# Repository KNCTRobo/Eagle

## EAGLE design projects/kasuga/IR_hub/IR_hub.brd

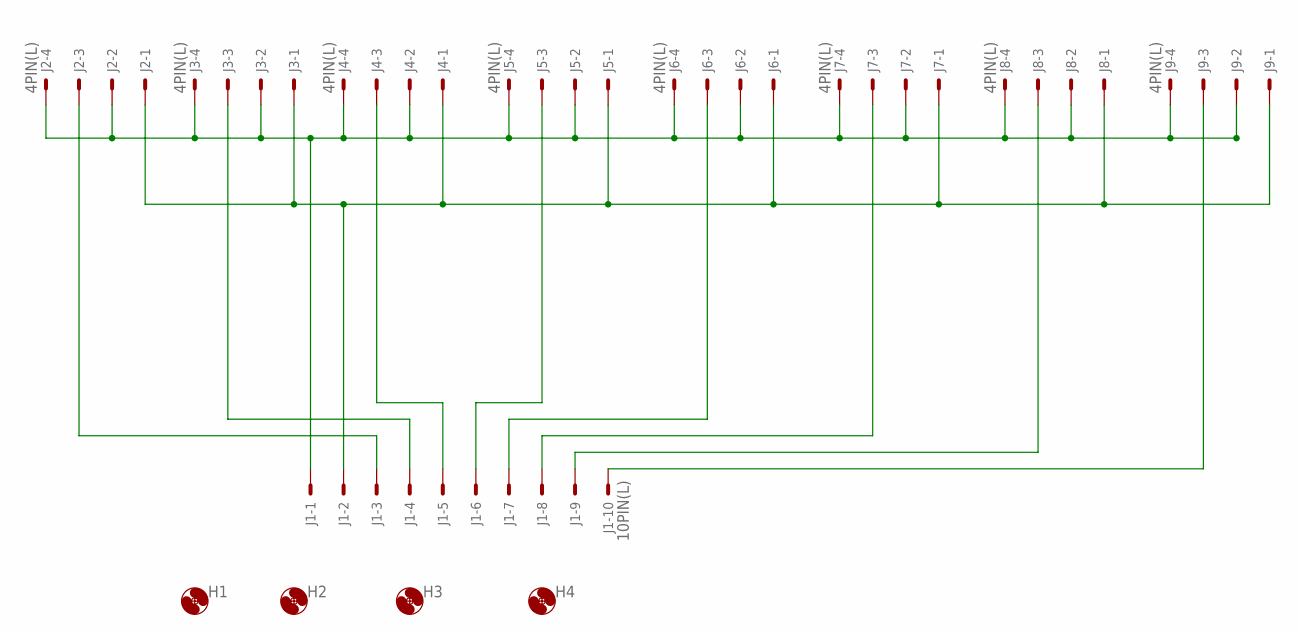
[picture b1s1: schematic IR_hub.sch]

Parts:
H1, H2, H3, H4: HOLE3.3M3BOLT; HOLE3.3
J1: 10PIN(L); 10PL
J2, J3, J4, J5, J6, J7, J8, J9: 4PIN(L); 4PL

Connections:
unnamed: J1.10, J9.3
unnamed: J1.9, J8.3
unnamed: J1.8, J7.3
unnamed: J1.7, J6.3
unnamed: J1.6, J5.3
unnamed: J1.5, J4.3
unnamed: J1.4, J3.3
unnamed: J1.3, J2.3
unnamed: J1.1, J2.2, J2.4, J3.2, J3.4, J4.2, J4.4, J5.2, J5.4, J6.2, J6.4, J7.2, J7.4, J8.2, J8.4, J9.2, J9.4
unnamed: J1.2, J2.1, J3.1, J4.1, J5.1, J6.1, J7.1, J8.1, J9.1

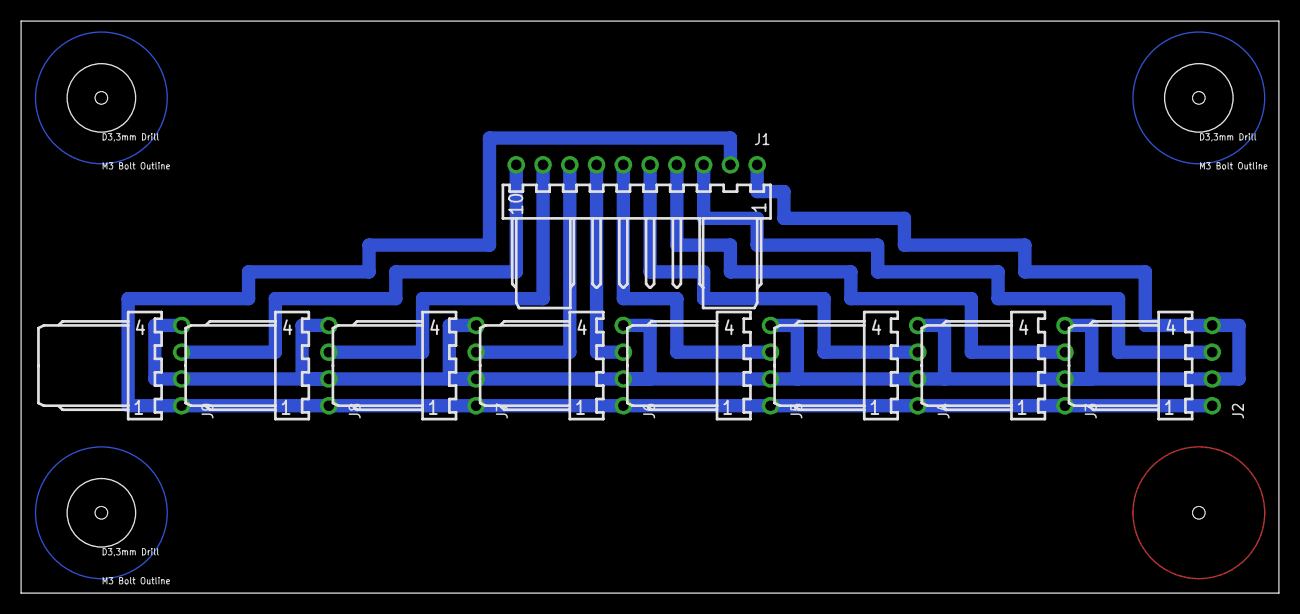
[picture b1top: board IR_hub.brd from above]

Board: 2 copper layers, 119.4 x 54.3 mm, 13 parts (1 on the bottom side), 10 nets.

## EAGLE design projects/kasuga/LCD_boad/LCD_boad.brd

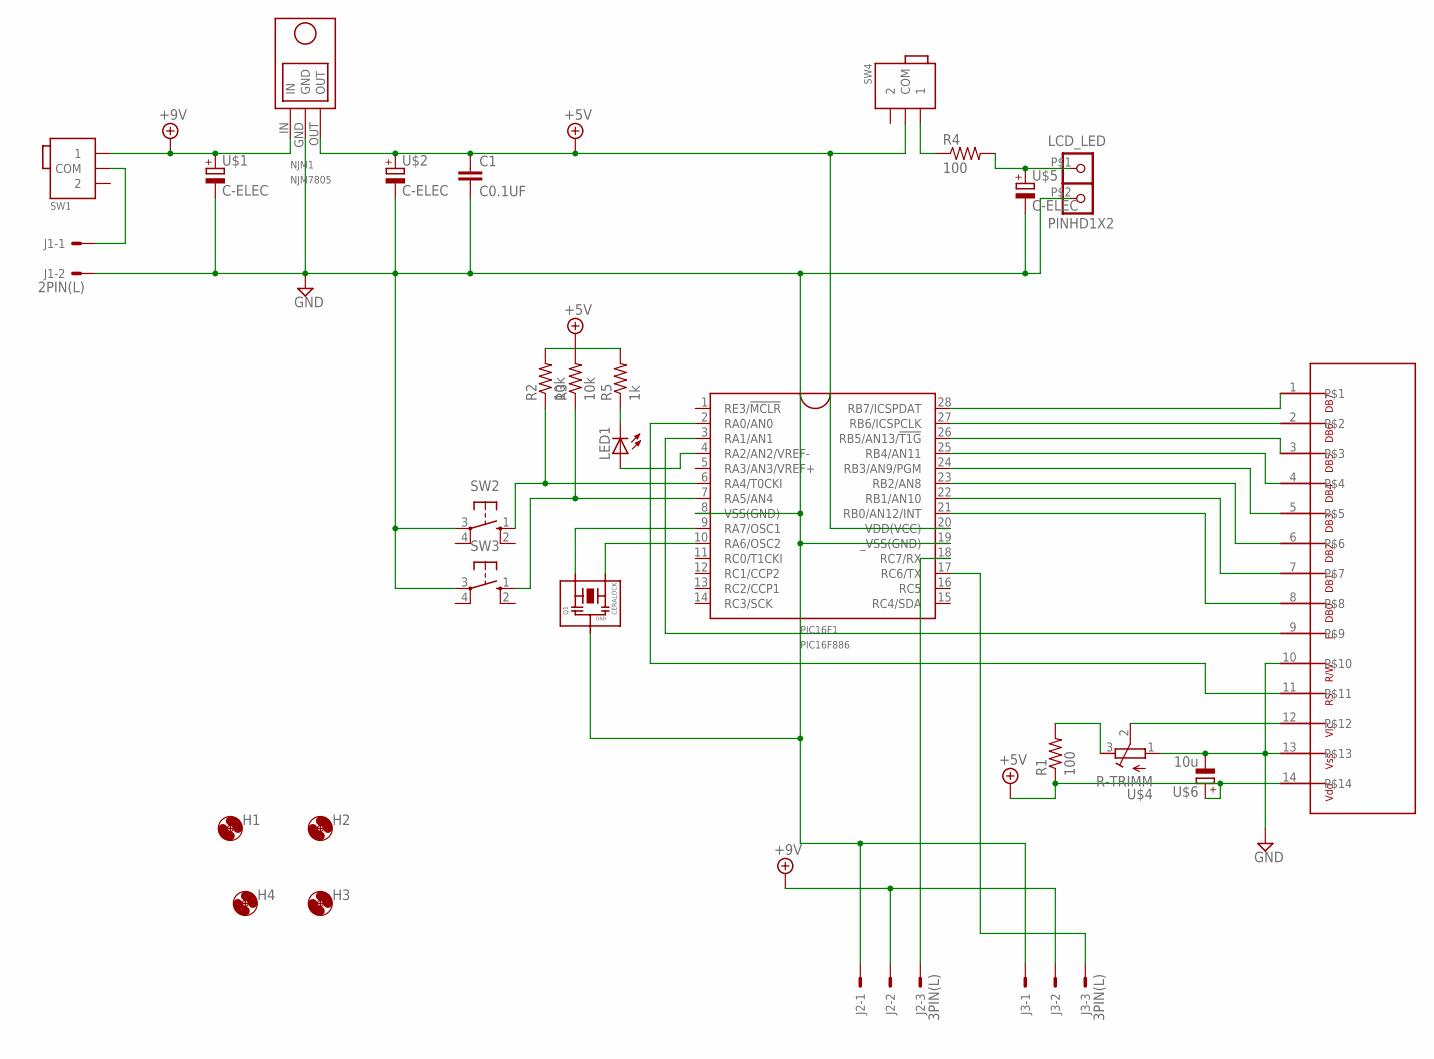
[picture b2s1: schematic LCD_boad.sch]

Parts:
C1: C0.1UF
H1, H2, H3, H4: HOLE3.3M3BOLT; HOLE3.3
J1: 2PIN(L); 2PL
J2, J3: 3PIN(L); 3PL
LCD_LED: PINHD1X2
LED1: LED; LED5MM
NJM1: NJM7805
PIC16F1: PIC16F886; DIL28-3
Q1: CERALOCK
R1, R4: 100; 0207/10
R2, R3: 10k; 0207/10
R5: 1k; 0207/10
SW1, SW4: SWITCH_MININORMAL; SWITCH_MINI
SW2, SW3: TACTSW; TACT
U$1, U$2, U$5: C-ELEC; C-6MM
U$3: L1672D1JOOO; Ｌ１６７２Ｄ１Ｊ０００
U$4: R-TRIMM
U$6: 10u; C-6MM

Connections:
+5V: C1.1, NJM1.OUT, PIC16F1.20 (VDD(VCC)), R1.1, R2.2, R3.2, R5.2, SW4.COM, U$2.+, U$3.14, U$6.+
+9V: J2.2, J3.2, NJM1.IN, SW1.1, U$1.+
GND: C1.2, J1.2, J2.1, J3.1, LCD_LED.P$2 (3), NJM1.GND, PIC16F1.8 (VSS(GND)), PIC16F1.19 (_VSS(GND)), Q1.P$2, SW2.3, SW3.3, U$1.-, U$2.-, U$3.10, U$3.13, U$4.1, U$5.-, U$6.-
unnamed: J1.1, SW1.COM
unnamed: J2.3, PIC16F1.18 (RC7/RX)
unnamed: R1.2, U$4.3
unnamed: J3.3, PIC16F1.17 (RC6/TX)
unnamed: PIC16F1.28 (RB7/ICSPDAT), U$3.1
unnamed: PIC16F1.27 (RB6/ICSPCLK), U$3.2
unnamed: PIC16F1.26 (RB5/AN13/!T1G), U$3.3
unnamed: PIC16F1.25 (RB4/AN11), U$3.4
unnamed: PIC16F1.24 (RB3/AN9/PGM), U$3.5
unnamed: PIC16F1.23 (RB2/AN8), U$3.6
unnamed: PIC16F1.22 (RB1/AN10), U$3.7
unnamed: PIC16F1.21 (RB0/AN12/INT), U$3.8
unnamed: PIC16F1.3 (RA1/AN1), U$3.9
unnamed: PIC16F1.2 (RA0/AN0), U$3.11
unnamed: U$3.12, U$4.2
unnamed: PIC16F1.6 (RA4/T0CKI), R2.1, SW2.1 (S)
unnamed: PIC16F1.7 (RA5/AN4), R3.1, SW3.1 (S)
unnamed: LCD_LED.P$1 (4), R4.2, U$5.+
unnamed: R4.1, SW4.1
unnamed: LED1.A, PIC16F1.4 (RA2/AN2/VREF-)
unnamed: LED1.K (C), R5.1
unnamed: PIC16F1.9 (RA7/OSC1), Q1.P$1
unnamed: PIC16F1.10 (RA6/OSC2), Q1.P$3

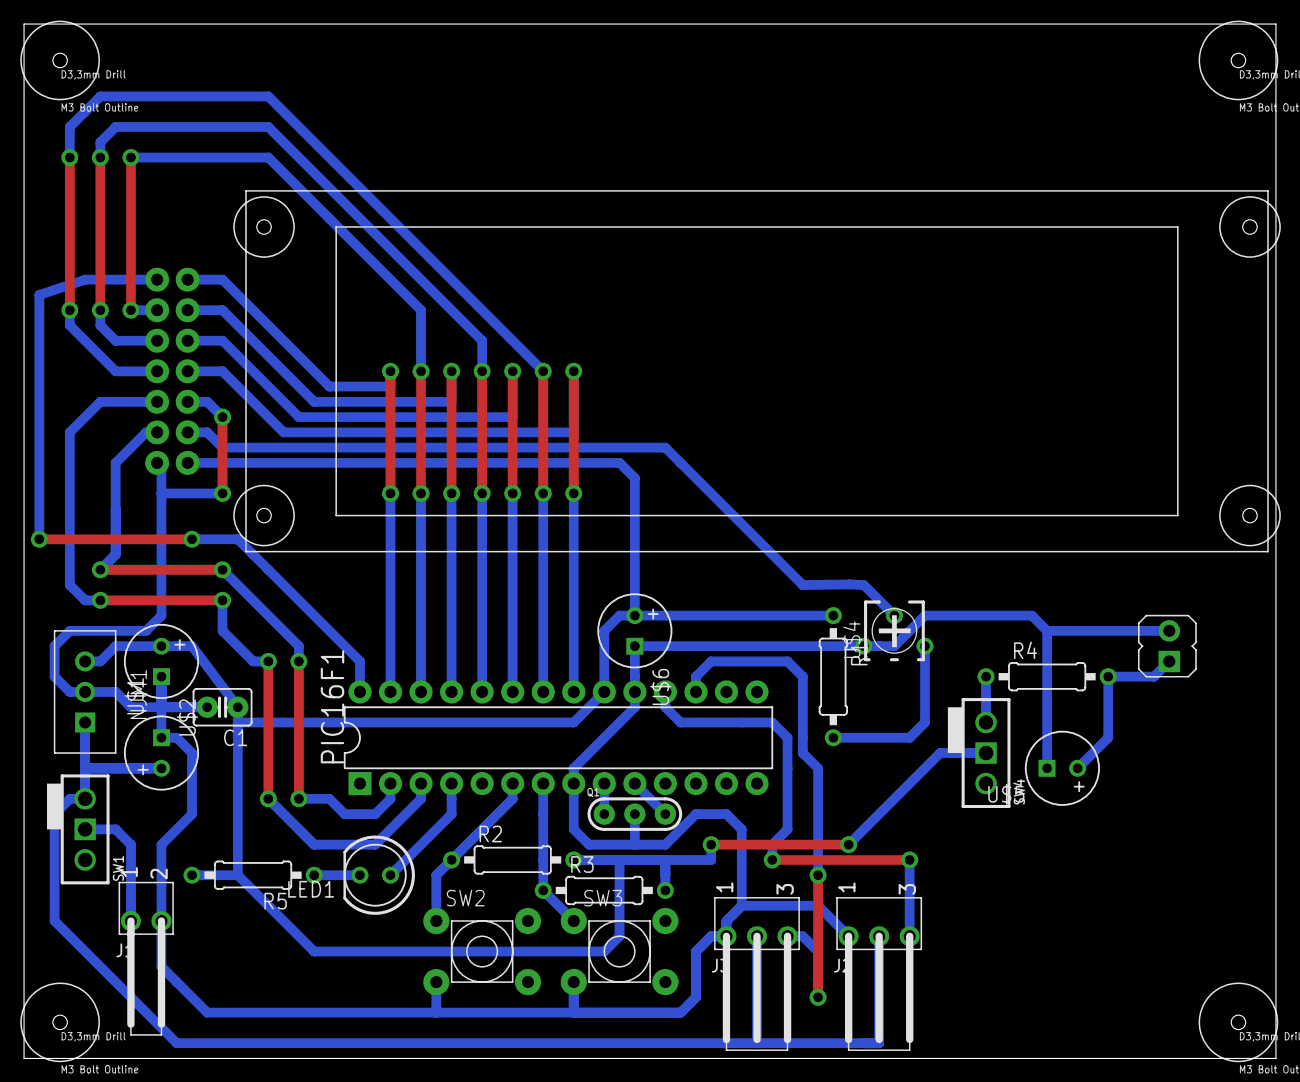
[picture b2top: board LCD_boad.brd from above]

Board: 2 copper layers, 104.1 x 86.0 mm, 28 parts (0 on the bottom side), 26 nets.

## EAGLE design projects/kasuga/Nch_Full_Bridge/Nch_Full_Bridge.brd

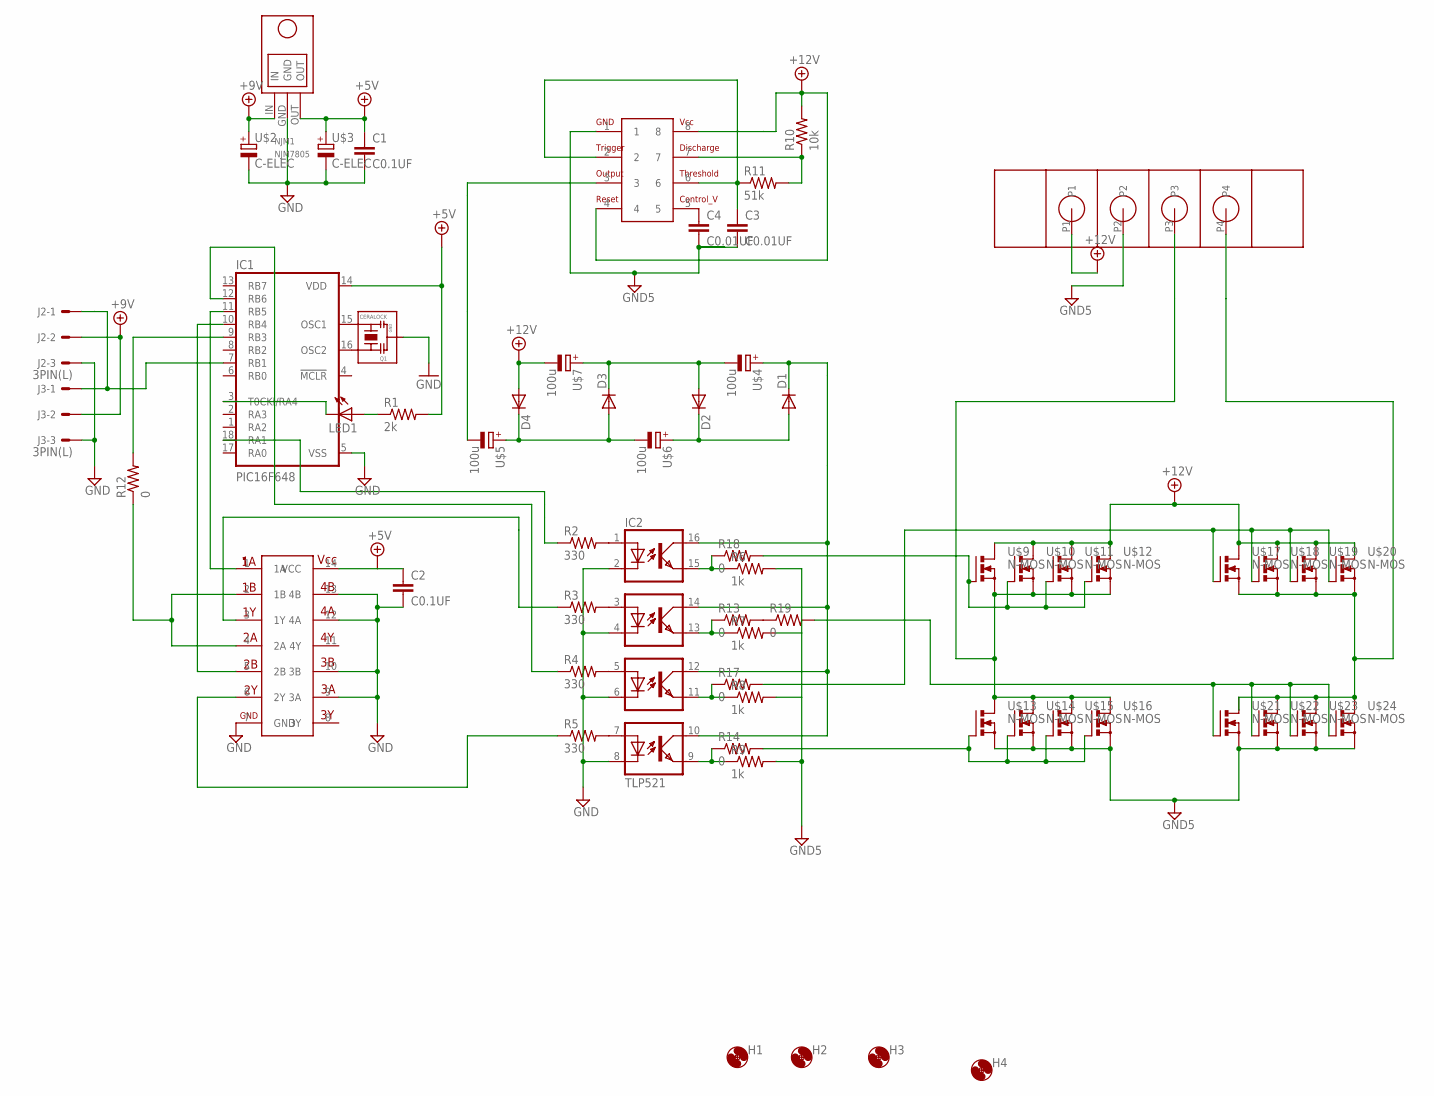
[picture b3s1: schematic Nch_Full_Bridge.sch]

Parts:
C1, C2: C0.1UF
C3, C4: C0.01UF; C0.1UF
D1, D2, D3, D4: DIODE7.5
H1, H2, H3, H4: HOLE3.3M3BOLT; HOLE3.3
IC1: PIC16F648; DIL18
IC2: TLP521; DIL16
J2, J3: 3PIN(L); 3PL
LED1: LED; LED5MM
NJM1: NJM7805
Q1: CERALOCK
R1: 2k; 0207/10
R2, R3, R4, R5: 330; 0207/10
R6, R7, R8, R9: 1k; 0207/10
R10: 10k; 0207/10
R11: 51k; 0207/10
R12, R13, R14, R17, R18, R19: 0; 0207/10
U$1: HD74HC08; DIL14
U$2, U$3: C-ELEC; C-6MM
U$4, U$5, U$6, U$7: 100u; C-6MM
U$8: NE555N; DIL08
U$9, U$10, U$11, U$12, U$13, U$14, U$15, U$16, U$17, U$18, U$19, U$20, U$21, U$22, U$23, U$24: N-MOS; TO220BV
U$25: BP341L

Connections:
+5V: C1.1, C2.1, IC1.14 (VDD), NJM1.OUT, R1.2, U$1.14 (VCC), U$3.+
+9V: J2.2, J3.2, NJM1.IN, U$2.+
+12V: D4.PA (A), R10.2, U$7.-, U$8.4, U$8.8, U$9.D, U$10.D, U$11.D, U$12.D, U$17.D, U$18.D, U$19.D, U$25.P1
GND: C1.2, C2.2, IC1.5 (VSS), IC2.2 (C0), IC2.4 (C1), IC2.6 (C2), IC2.8 (C3), J2.3, J3.3, NJM1.GND, Q1.P$2, U$1.7 (GND), U$1.9 (3A), U$1.10 (3B), U$1.12 (4A), U$1.13 (4B), U$2.-, U$3.-
GND5: C3.2, C4.2, R6.2, R7.2, R8.2, R9.2, U$8.1, U$13.S, U$14.S, U$15.S, U$16.S, U$21.S, U$22.S, U$23.S, U$24.S, U$25.P2
unnamed: IC1.16 (OSC2), Q1.P$1
unnamed: IC1.15 (OSC1), Q1.P$3
unnamed: IC1.3 (T0CKI/RA4), LED1.K (C)
unnamed: LED1.A, R1.1
unnamed: IC2.7 (A3), R5.2
unnamed: IC1.9 (RB3), R12.2
unnamed: IC1.18 (RA1), R2.1
unnamed: IC1.12 (RB6), R4.1
unnamed: R3.1, U$1.3 (1Y)
unnamed: R5.1, U$1.6 (2Y)
unnamed: R12.1, U$1.2 (1B), U$1.4 (2A)
unnamed: IC1.11 (RB5), U$1.1 (1A)
unnamed: IC1.10 (RB4), U$1.5 (2B)
unnamed: IC2.1 (A0), R2.2
unnamed: IC2.3 (A1), R3.2
unnamed: IC2.5 (A2), R4.2
unnamed: R10.1, R11.2, U$8.7
unnamed: D1.PK (C), IC2.10 (COL3), IC2.12 (COL2), IC2.14 (COL1), IC2.16 (COL0), U$4.+
unnamed: D1.PA (A), D2.PK (C), U$6.+
unnamed: D2.PA (A), D3.PK (C), U$4.-, U$7.+
unnamed: C3.1, R11.1, U$8.2, U$8.6
unnamed: D3.PA (A), D4.PK (C), U$5.+, U$6.-
unnamed: C4.1, U$8.5
unnamed: U$5.-, U$8.3
unnamed: R18.2, U$9.G, U$10.G, U$11.G, U$12.G
unnamed: R19.2, U$21.G, U$22.G, U$23.G, U$24.G
unnamed: R17.2, U$17.G, U$18.G, U$19.G, U$20.G
unnamed: R14.2, U$13.G, U$14.G, U$15.G, U$16.G
unnamed: IC2.11 (EMIT2), R8.1, R17.1
unnamed: U$9.S, U$10.S, U$11.S, U$12.S, U$13.D, U$14.D, U$15.D, U$16.D, U$25.P3
unnamed: IC1.7 (RB1), J2.1, J3.1
unnamed: IC2.13 (EMIT1), R7.1, R13.1
unnamed: IC2.9 (EMIT3), R9.1, R14.1
unnamed: IC2.15 (EMIT0), R6.1, R18.1
unnamed: U$17.S, U$18.S, U$19.S, U$20.S, U$22.D, U$23.D, U$24.D, U$25.P4
unnamed: R13.2, R19.1

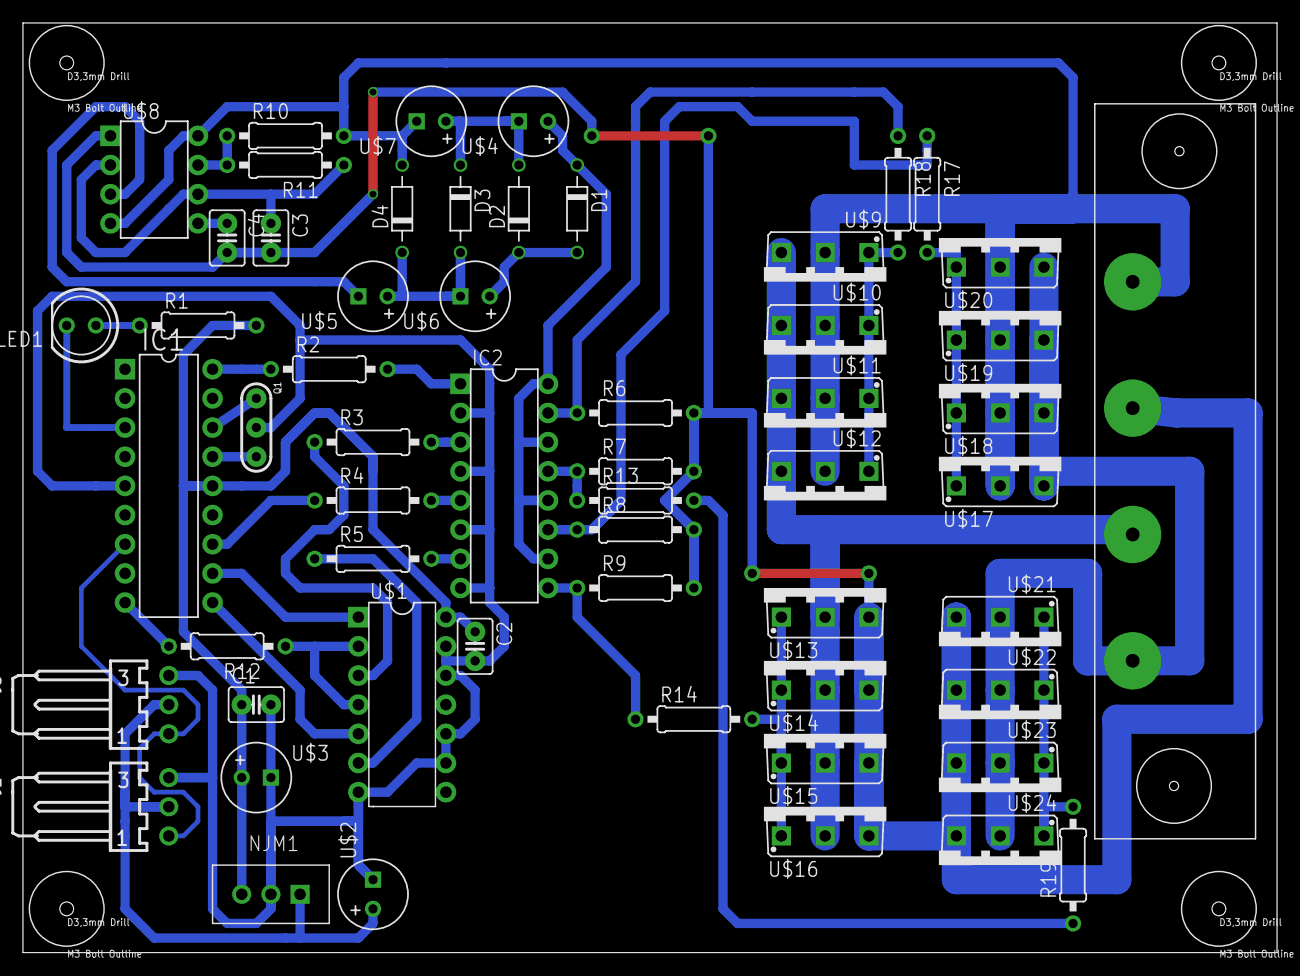
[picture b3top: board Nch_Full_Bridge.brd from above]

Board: 2 copper layers, 109.2 x 81.0 mm, 61 parts (0 on the bottom side), 41 nets.

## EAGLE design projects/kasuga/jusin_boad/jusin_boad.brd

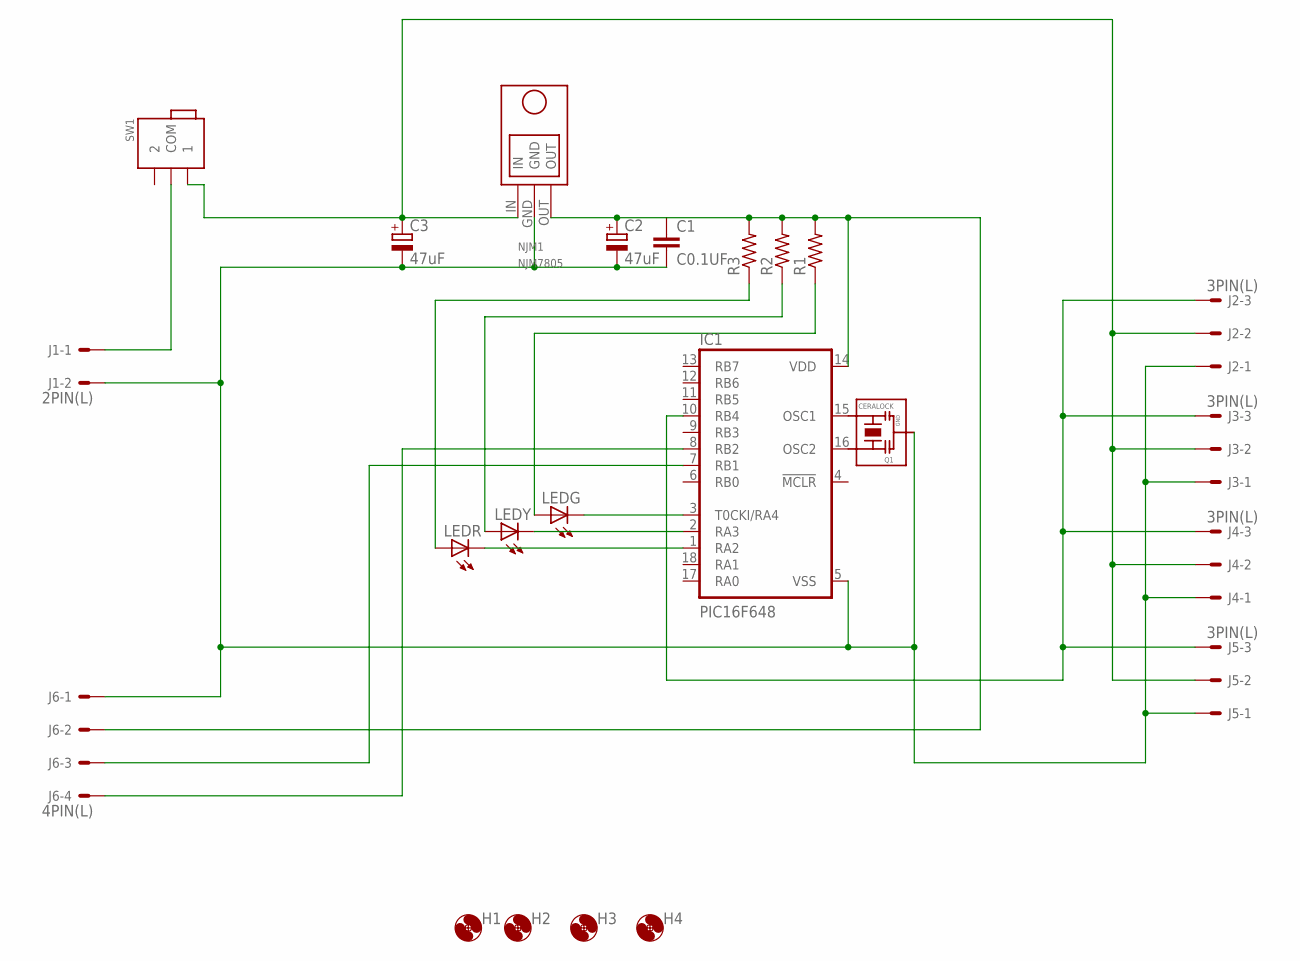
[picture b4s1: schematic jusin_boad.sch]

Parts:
C1: C0.1UF
C2, C3: 47uF; C-6MM
H1, H2, H3, H4: HOLE3.3M3BOLT; HOLE3.3
IC1: PIC16F648; DIL18
J1: 2PIN(L); 2PL
J2, J3, J4, J5: 3PIN(L); 3PL
J6: 4PIN(L); 4PL
LEDG: LED; LED5MM
LEDR: LED; LED5MM
LEDY: LED; LED5MM
NJM1: NJM7805
Q1: CERALOCK
R1, R2, R3: R-; 0207/10
SW1: SWITCH_MININORMAL; SWITCH_MINI

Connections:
unnamed: IC1.16 (OSC2), Q1.P$1
unnamed: IC1.15 (OSC1), Q1.P$3
unnamed: J1.1, SW1.COM
unnamed: C3.+, J2.2, J3.2, J4.2, J5.2, NJM1.IN, SW1.1
unnamed: C1.2, C2.-, C3.-, IC1.5 (VSS), J1.2, J2.1, J3.1, J4.1, J5.1, J6.1, NJM1.GND, Q1.P$2
unnamed: C1.1, C2.+, IC1.14 (VDD), J6.2, NJM1.OUT, R1.2, R2.2, R3.2
unnamed: IC1.10 (RB4), J2.3, J3.3, J4.3, J5.3
unnamed: LEDR.A, R3.1
unnamed: LEDG.A, R1.1
unnamed: LEDY.A, R2.1
unnamed: IC1.3 (T0CKI/RA4), LEDG.K (C)
unnamed: IC1.2 (RA3), LEDY.K (C)
unnamed: IC1.1 (RA2), LEDR.K (C)
unnamed: IC1.7 (RB1), J6.3
unnamed: IC1.8 (RB2), J6.4

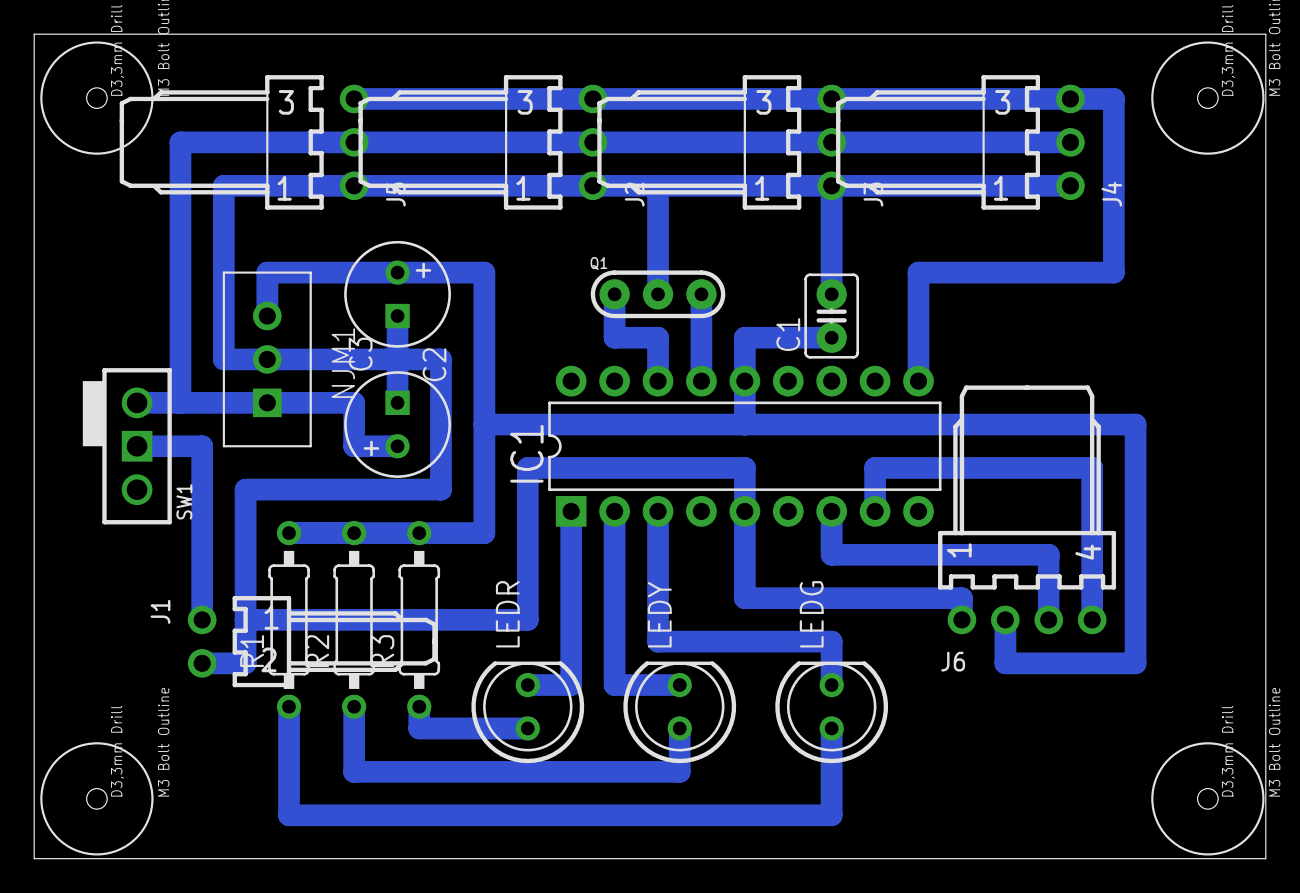
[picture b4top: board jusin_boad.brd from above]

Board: 2 copper layers, 72.1 x 48.2 mm, 23 parts (0 on the bottom side), 15 nets.

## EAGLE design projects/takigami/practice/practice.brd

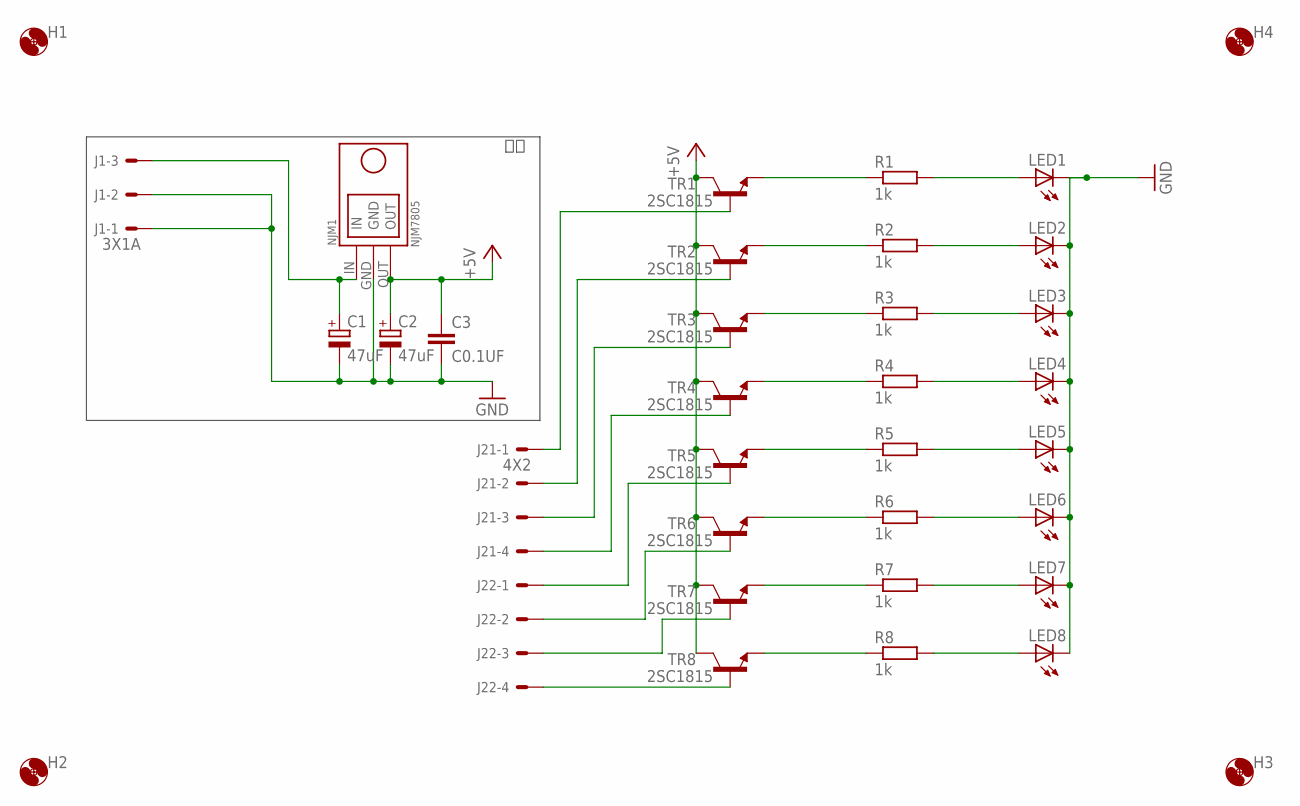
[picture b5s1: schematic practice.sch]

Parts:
C1, C2: 47uF; E2-5
C3: C0.1UF
H1, H2, H3, H4: HOLE3.3M3BOLT; HOLE3.3
J1: 3X1A; 37203-62A3-003
J2: 4X2; 37208-62A3-004
LED1, LED2, LED3, LED4, LED5, LED6, LED7, LED8: LED5MM
NJM1: NJM7805
R1, R2, R3, R4, R5, R6, R7, R8: 1k; R3216W
TR1, TR2, TR3, TR4, TR5, TR6, TR7, TR8: 2SC1815; TO92-

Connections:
+5V: C2.+, C3.1, NJM1.OUT, TR1.C, TR2.C, TR3.C, TR4.C, TR5.C, TR6.C, TR7.C, TR8.C
GND: C1.-, C2.-, C3.2, J1.1-1, J1.1-2, LED1.K (C), LED2.K (C), LED3.K (C), LED4.K (C), LED5.K (C), LED6.K (C), LED7.K (C), LED8.K (C), NJM1.GND
unnamed: C1.+, J1.1-3, NJM1.IN
unnamed: R1.1, TR1.E
unnamed: R2.1, TR2.E
unnamed: R3.1, TR3.E
unnamed: R4.1, TR4.E
unnamed: R5.1, TR5.E
unnamed: R6.1, TR6.E
unnamed: R7.1, TR7.E
unnamed: R8.1, TR8.E
unnamed: LED5.A, R5.2
unnamed: LED6.A, R6.2
unnamed: LED7.A, R7.2
unnamed: LED8.A, R8.2
unnamed: LED1.A, R1.2
unnamed: LED2.A, R2.2
unnamed: LED3.A, R3.2
unnamed: LED4.A, R4.2
unnamed: J2.1-1, TR1.B
unnamed: J2.1-2, TR2.B
unnamed: J2.1-3, TR3.B
unnamed: J2.1-4, TR4.B
unnamed: J2.2-1, TR5.B
unnamed: J2.2-2, TR6.B
unnamed: J2.2-3, TR7.B
unnamed: J2.2-4, TR8.B

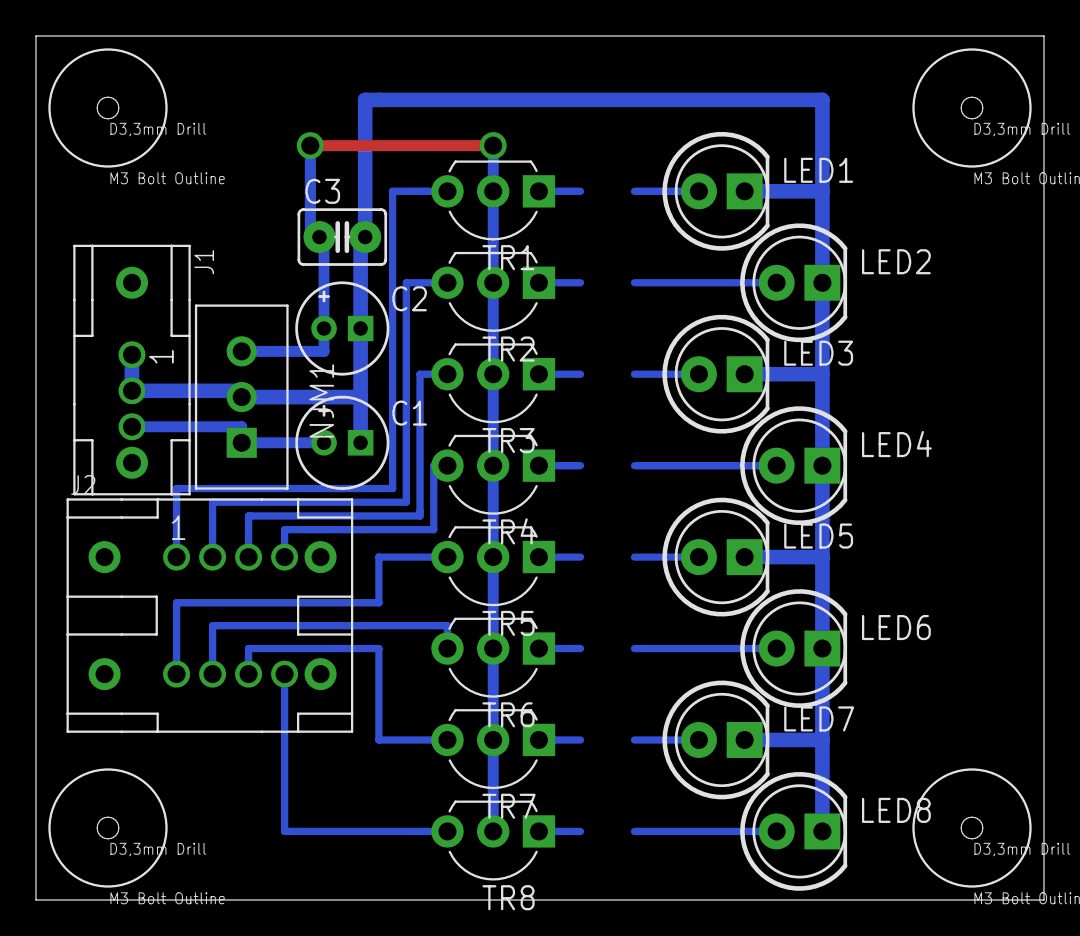
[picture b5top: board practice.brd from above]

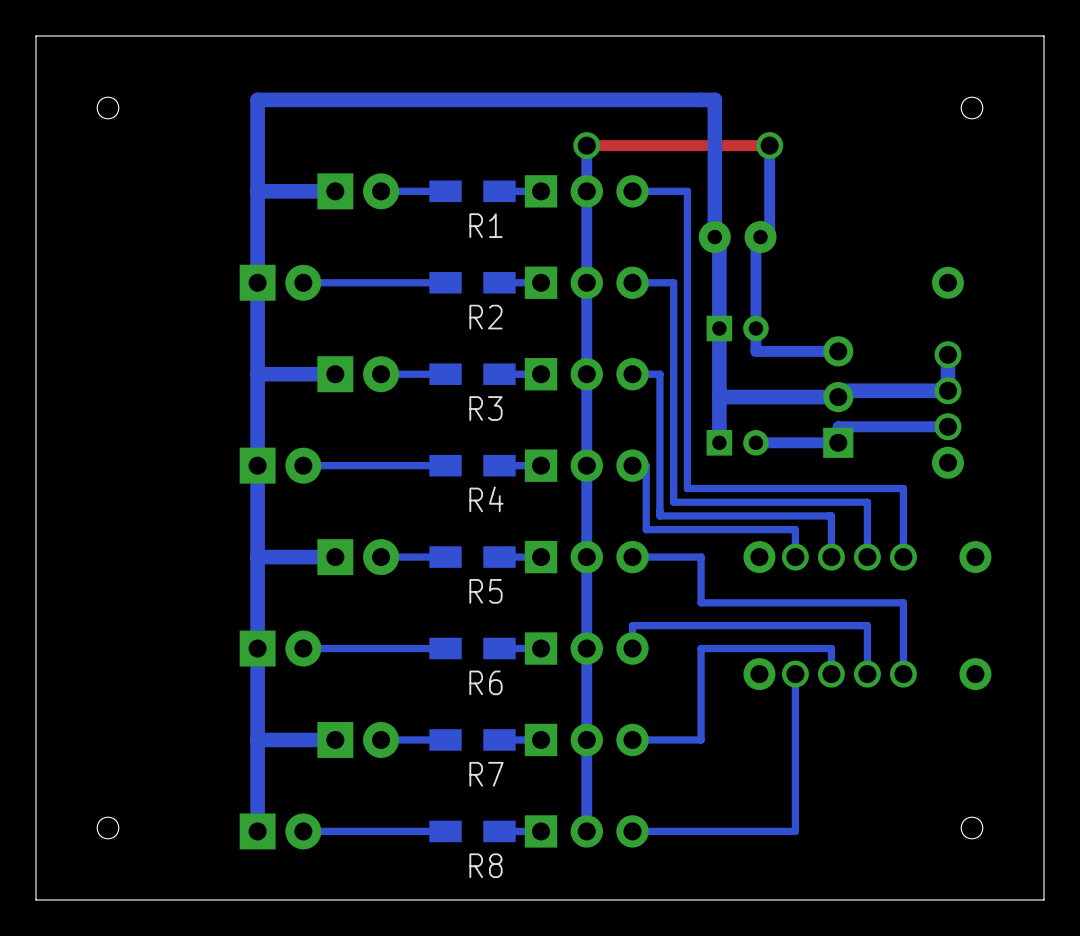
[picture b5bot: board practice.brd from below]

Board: 2 copper layers, 56.0 x 48.0 mm, 34 parts (8 on the bottom side), 27 nets.
